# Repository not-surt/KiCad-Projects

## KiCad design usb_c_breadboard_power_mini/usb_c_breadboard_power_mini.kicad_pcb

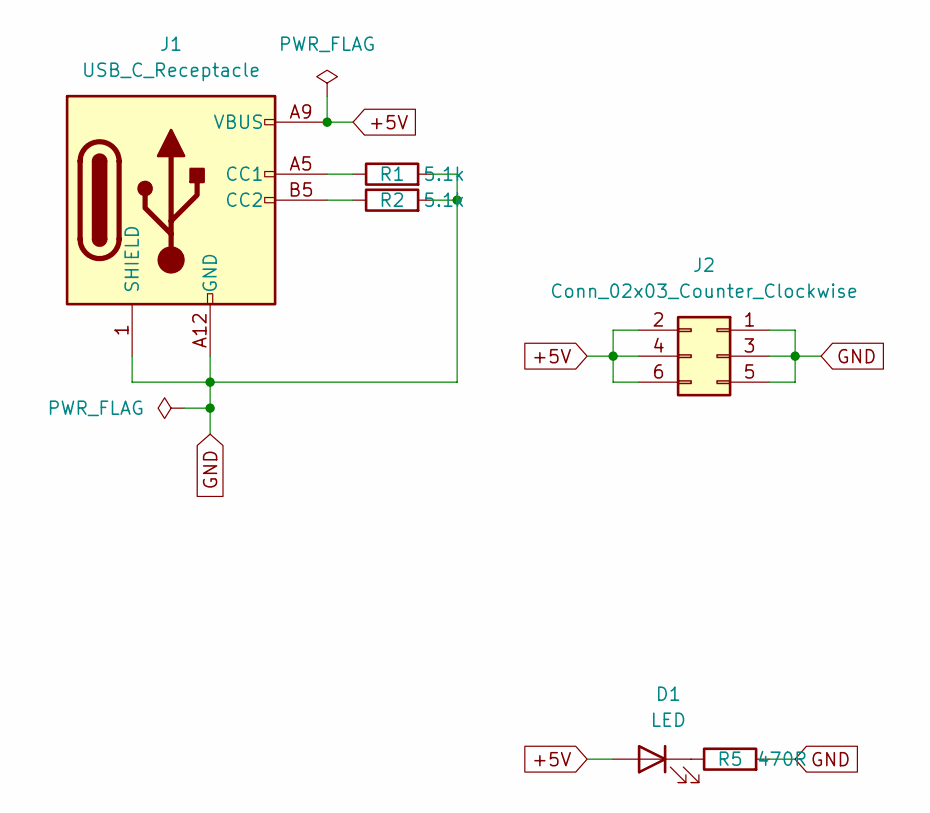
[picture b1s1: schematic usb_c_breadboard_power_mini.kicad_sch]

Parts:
D1: LED; LED_0805_2012Metric_Pad1.15x1.40mm_HandSolder
J1: USB_C_Receptacle; TYPE-C-31-M-17_handsolder
J2: Conn_02x03_Counter_Clockwise; PinHeader_2x03_P2.54mm_Vertical_SMD
R1, R2: 5.1k; R_0805_2012Metric_Pad1.20x1.40mm_HandSolder
R5: 470R; R_0805_2012Metric_Pad1.20x1.40mm_HandSolder

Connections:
+5V: D1.2 (A), J1.A9 (VBUS), J1.B9 (VBUS), J2.2, J2.4, J2.6
GND: J1.1 (SHIELD), J1.A12 (GND), J1.B12 (GND), J2.1, J2.3, J2.5, R1.2, R2.2, R5.2
unnamed: D1.1 (K), R5.1
unnamed: J1.A5 (CC1), R1.1
unnamed: J1.B5 (CC2), R2.1

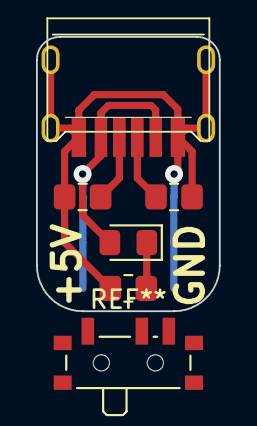
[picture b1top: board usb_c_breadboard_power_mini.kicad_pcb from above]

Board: 2 copper layers, 10.2 x 15.2 mm, 6 parts (1 on the bottom side), 5 nets.

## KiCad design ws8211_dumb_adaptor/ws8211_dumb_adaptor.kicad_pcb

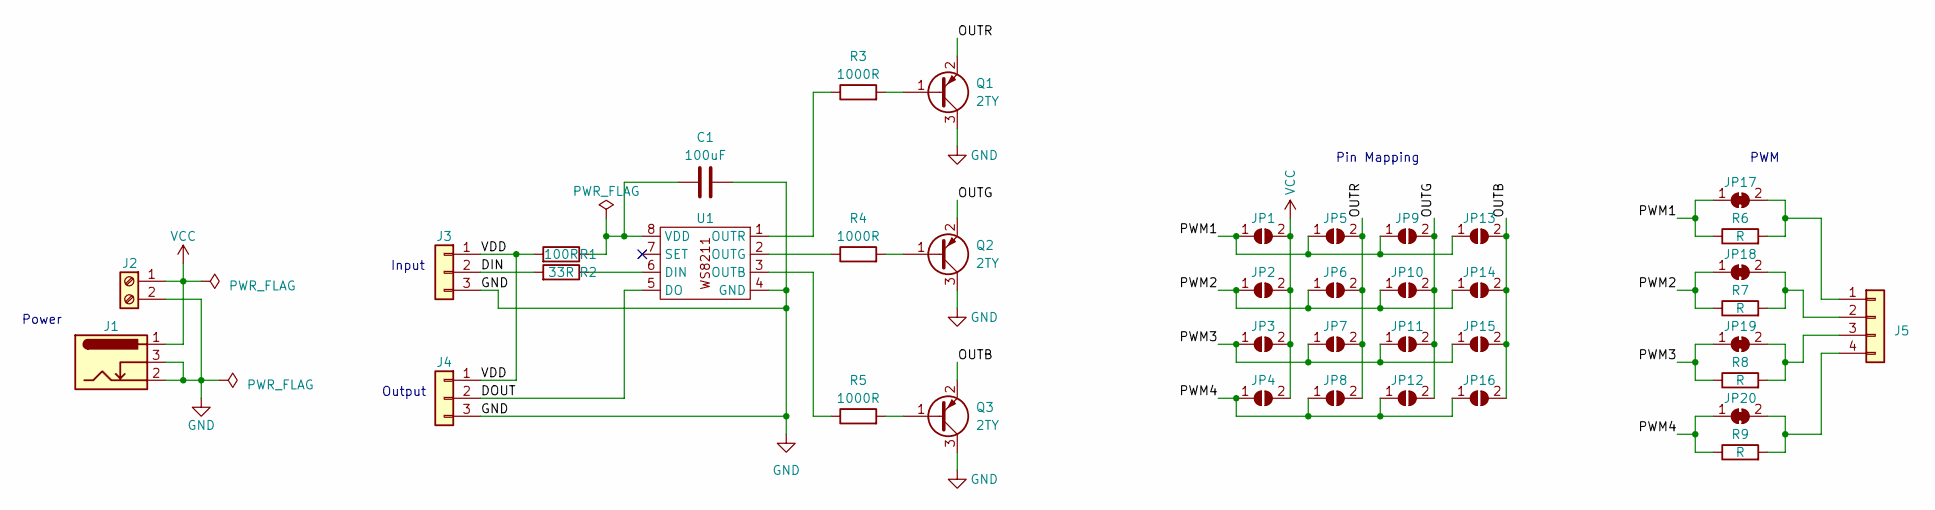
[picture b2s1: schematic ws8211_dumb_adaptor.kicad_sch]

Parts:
C1: 100uF; CP_Radial_D7.5mm_P2.50mm
J1: Barrel_Jack_Switch; BarrelJack_Horizontal
J2: Screw_Terminal_01x02; TerminalBlock_bornier-2_P5.08mm
J3, J4: Conn_01x03; PinHeader_1x03_P2.54mm_Vertical
J5: Conn_01x04; PinHeader_1x04_P2.54mm_Vertical
JP1, JP2, JP3, JP4, JP5, JP6, JP7, JP8, JP9, JP10, JP11, JP12, JP13, JP14, JP15, JP16: SolderJumper_2_Open; SolderJumper-2_P1.3mm_Open_RoundedPad1.0x1.5mm
JP17, JP18, JP19, JP20: SolderJumper_2_Bridged; SolderJumper-2_P1.3mm_Bridged_RoundedPad1.0x1.5mm
Q1, Q2, Q3: 2TY; SOT-23
R1: 100R; R_1206_3216Metric_Pad1.30x1.75mm_HandSolder
R2: 33R; R_1206_3216Metric_Pad1.30x1.75mm_HandSolder
R3, R4, R5: 1000R; R_1206_3216Metric_Pad1.30x1.75mm_HandSolder
R6, R7, R8, R9: R; R_1206_3216Metric_Pad1.30x1.75mm_HandSolder
U1: SOP-8_3.9x4.9mm_P1.27mm

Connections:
/DIN: J3.2, R2.2
/DOUT: J4.2, U1.5 (DO)
/OUTB: JP13.2 (B), JP14.2 (B), JP15.2 (B), JP16.2 (B), Q3.2 (E)
/OUTG: JP9.2 (B), JP10.2 (B), JP11.2 (B), JP12.2 (B), Q2.2 (E)
/OUTR: JP5.2 (B), JP6.2 (B), JP7.2 (B), JP8.2 (B), Q1.2 (E)
/PWM1: JP1.1 (A), JP5.1 (A), JP9.1 (A), JP13.1 (A), JP17.1 (A), R6.1
/PWM2: JP2.1 (A), JP6.1 (A), JP10.1 (A), JP14.1 (A), JP18.1 (A), R7.1
/PWM3: JP3.1 (A), JP7.1 (A), JP11.1 (A), JP15.1 (A), JP19.1 (A), R8.1
/PWM4: JP4.1 (A), JP8.1 (A), JP12.1 (A), JP16.1 (A), JP20.1 (A), R9.1
/VDD: J3.1, J4.1, R1.2
GND: C1.2, J1.2, J1.3, J2.2, J3.3, J4.3, Q1.3 (C), Q2.3 (C), Q3.3 (C), U1.4 (GND)
unnamed: J5.1, JP17.2 (B), R6.2
unnamed: J5.2, JP18.2 (B), R7.2
unnamed: J5.3, JP19.2 (B), R8.2
unnamed: J5.4, JP20.2 (B), R9.2
unnamed: Q1.1 (B), R3.2
unnamed: Q2.1 (B), R4.2
unnamed: Q3.1 (B), R5.2
unnamed: R2.1, U1.6 (DIN)
unnamed: R5.1, U1.3 (OUTB)
unnamed: R4.1, U1.2 (OUTG)
unnamed: R3.1, U1.1 (OUTR)
unnamed: C1.1, R1.1, U1.8 (VDD)
VCC: J1.1, J2.1, JP1.2 (B), JP2.2 (B), JP3.2 (B), JP4.2 (B)

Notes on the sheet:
Output
Input
Power
PWM
Pin Mapping

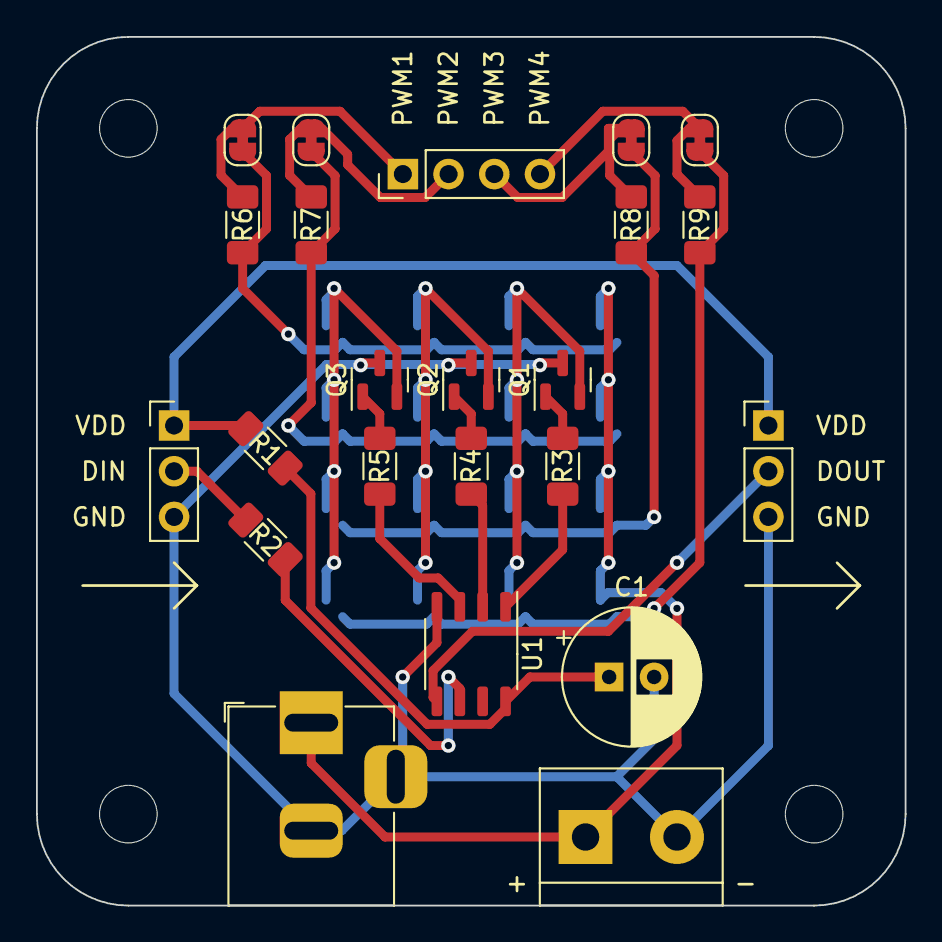
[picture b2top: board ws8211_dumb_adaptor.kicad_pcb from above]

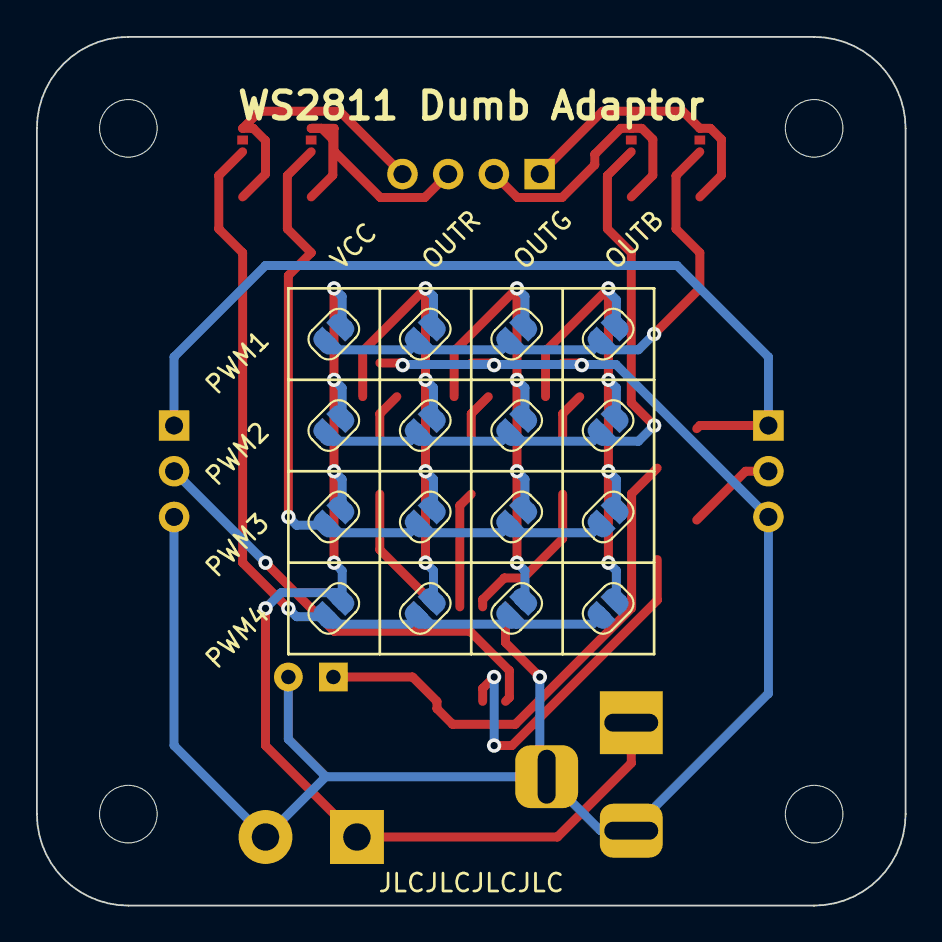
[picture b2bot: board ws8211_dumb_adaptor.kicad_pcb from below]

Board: 2 copper layers, 48.3 x 48.3 mm, 39 parts (16 on the bottom side), 24 nets.

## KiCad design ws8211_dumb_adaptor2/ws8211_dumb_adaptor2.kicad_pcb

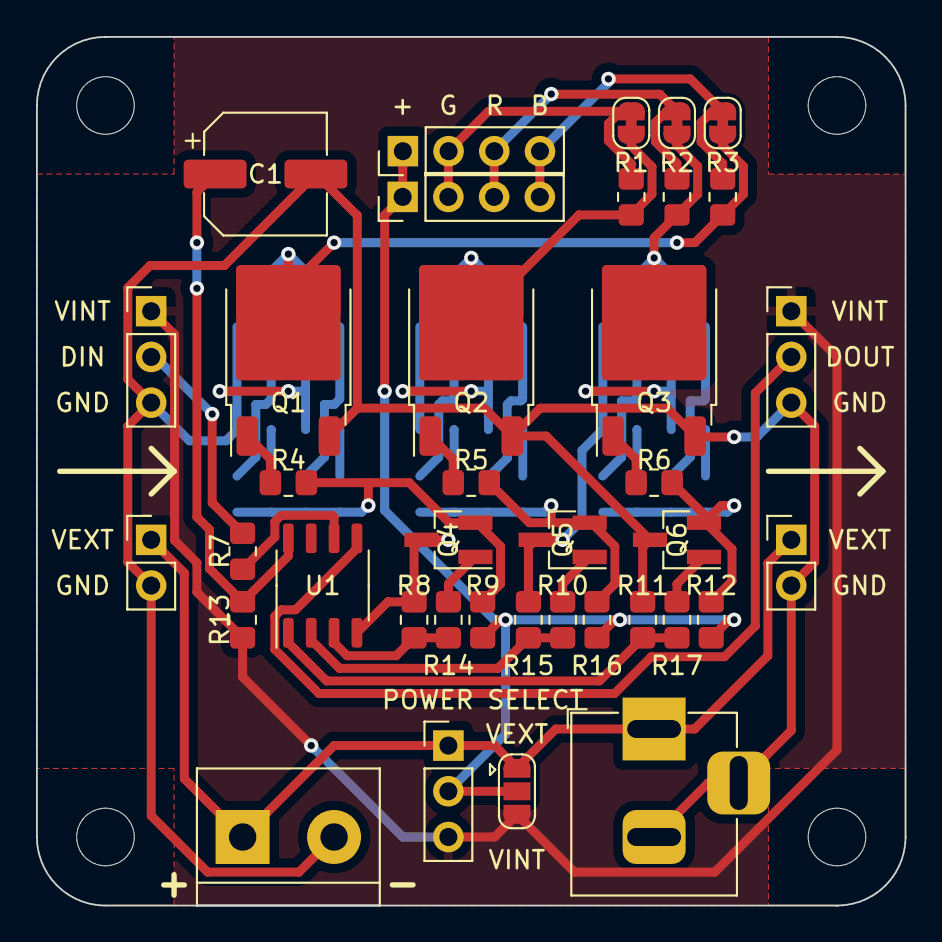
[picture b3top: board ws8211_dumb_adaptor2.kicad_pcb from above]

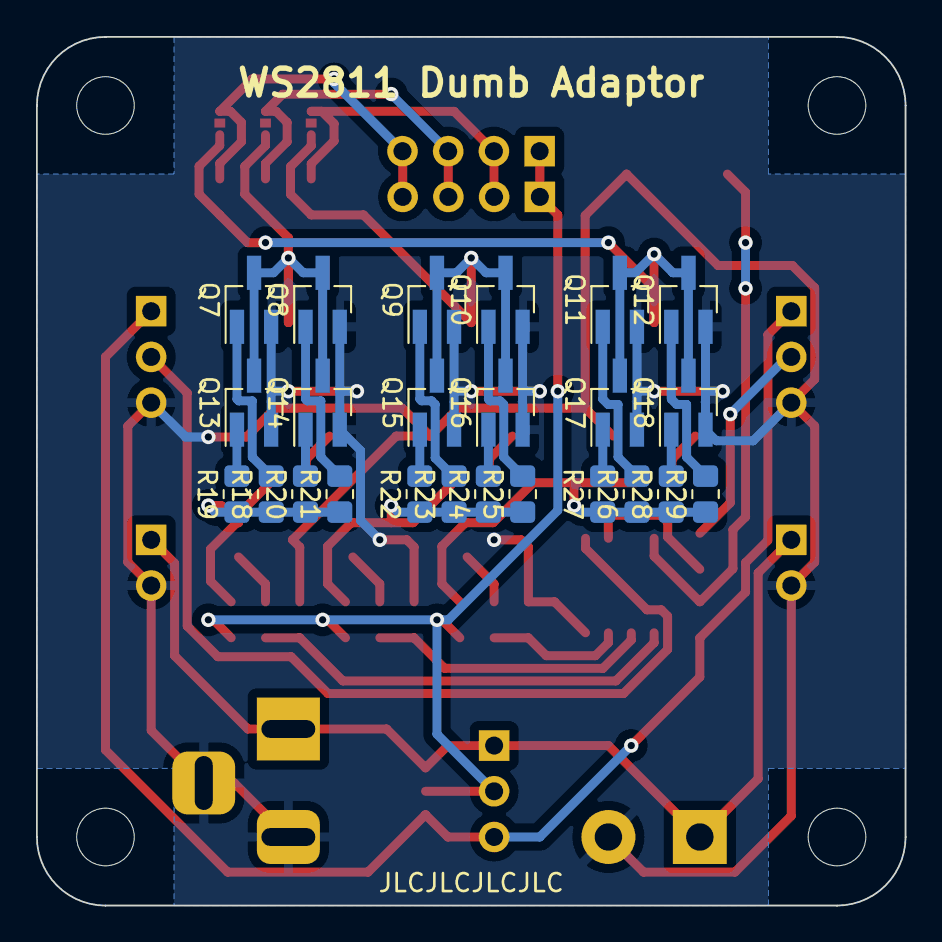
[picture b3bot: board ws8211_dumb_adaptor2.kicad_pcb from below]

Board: 2 copper layers, 48.3 x 48.3 mm, 62 parts (24 on the bottom side), 38 nets.

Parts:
C1: 100uF; CP_Elec_6.3x5.4
J1, J2: Conn_01x04; PinHeader_1x04_P2.54mm_Vertical
J3, J4: Conn_01x03; PinHeader_1x03_P2.54mm_Vertical
J5, J6: Conn_01x02; PinHeader_1x02_P2.54mm_Vertical
J7: Screw_Terminal_01x02; TerminalBlock_bornier-2_P5.08mm
J8: Barrel_Jack_Switch; BarrelJack_Horizontal
JP1, JP2, JP3: SolderJumper_2_Bridged; SolderJumper-2_P1.3mm_Bridged_RoundedPad1.0x1.5mm
JP4: Jumper_3_Open; PinHeader_1x03_P2.54mm_Vertical
JP5: SolderJumper_3_Open; SolderJumper-3_P1.3mm_Open_RoundedPad1.0x1.5mm
Q1, Q2, Q3: N-CHANNEL POWER MOSFET; TO-252-2
Q4, Q5, Q6: 2TY; SOT-23_Handsoldering
Q7, Q8, Q9, Q10, Q11, Q12, Q13, Q14, Q15, Q16, Q17, Q18: 2N7002K; SOT-23_Handsoldering
R1, R2, R3: R; R_0805_2012Metric_Pad1.20x1.40mm_HandSolder
R4, R5, R6, R10, R14, R17, R18, R19, R20, R21, R22, R23, R24, R25, R26, R27, R28, R29: 1000R; R_0805_2012Metric_Pad1.20x1.40mm_HandSolder
R7: 33R; R_0805_2012Metric_Pad1.20x1.40mm_HandSolder
R8, R9, R11, R12, R15, R16: 10K; R_0805_2012Metric_Pad1.20x1.40mm_HandSolder
R13: 100R; R_0805_2012Metric_Pad1.20x1.40mm_HandSolder
U1: SOP-8_3.9x4.9mm_P1.27mm

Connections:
/DIN: J3.2, R7.2
/DOUT: J4.2, U1.5 (DO)
/OUTB: R8.2, R14.1, U1.3 (OUTB)
/OUTG: R10.1, R15.2, U1.2 (OUTG)
/OUTR: R11.2, R17.1, U1.1 (OUTR)
/STRIPB: JP3.1 (A), Q1.2 (D), Q11.3 (D), Q12.3 (D), Q17.3 (D), Q18.3 (D), R3.1
/STRIPG: JP1.1 (A), Q2.2 (D), Q9.3 (D), Q10.3 (D), Q15.3 (D), Q16.3 (D), R1.1
/STRIPR: JP2.1 (A), Q3.2 (D), Q7.3 (D), Q8.3 (D), Q13.3 (D), Q14.3 (D), R2.1
/VDD: J3.1, J4.1, JP4.3 (B), JP5.3 (B), R13.2
/VSTRIP: J1.1, J2.1, JP4.2 (C), JP5.2 (C), R9.2, R12.2, R16.2
GND: C1.2, J3.3, J4.3, J5.2, J6.2, J7.2, J8.2, J8.3, Q1.3 (S), Q2.3 (S), Q3.3 (S), Q4.3 (C), Q5.3 (C), Q6.3 (C), Q7.2 (S), Q8.2 (S), Q9.2 (S), Q10.2 (S), Q11.2 (S), Q12.2 (S), Q13.2 (S), Q14.2 (S), Q15.2 (S), Q16.2 (S), Q17.2 (S), Q18.2 (S), R8.1, R11.1, R15.1, U1.4 (GND)
unnamed: J1.2, J2.2, JP1.2 (B), R1.2
unnamed: J1.3, J2.3, JP2.2 (B), R2.2
unnamed: J1.4, J2.4, JP3.2 (B), R3.2
unnamed: Q6.1 (B), R17.2
unnamed: Q6.2 (E), R6.1, R12.1, R18.1, R19.1, R20.1, R21.1
unnamed: Q3.1 (G), R6.2
unnamed: Q2.1 (G), R5.2
unnamed: Q5.1 (B), R10.2
unnamed: Q5.2 (E), R5.1, R16.1, R22.1, R23.1, R24.1, R25.1
unnamed: Q1.1 (G), R4.2
unnamed: Q4.1 (B), R14.2
unnamed: Q4.2 (E), R4.1, R9.1, R26.1, R27.1, R28.1, R29.1
unnamed: Q10.1 (G), R25.2
unnamed: Q16.1 (G), R24.2
unnamed: Q14.1 (G), R20.2
unnamed: Q7.1 (G), R18.2
unnamed: Q9.1 (G), R23.2
unnamed: Q13.1 (G), R19.2
unnamed: Q8.1 (G), R21.2
unnamed: Q17.1 (G), R27.2
unnamed: Q11.1 (G), R26.2
unnamed: Q15.1 (G), R22.2
unnamed: Q18.1 (G), R28.2
unnamed: Q12.1 (G), R29.2
unnamed: R7.1, U1.6 (DIN)
unnamed: C1.1, R13.1, U1.8 (VDD)
VCC: J5.1, J6.1, J7.1, J8.1, JP4.1 (A), JP5.1 (A)
